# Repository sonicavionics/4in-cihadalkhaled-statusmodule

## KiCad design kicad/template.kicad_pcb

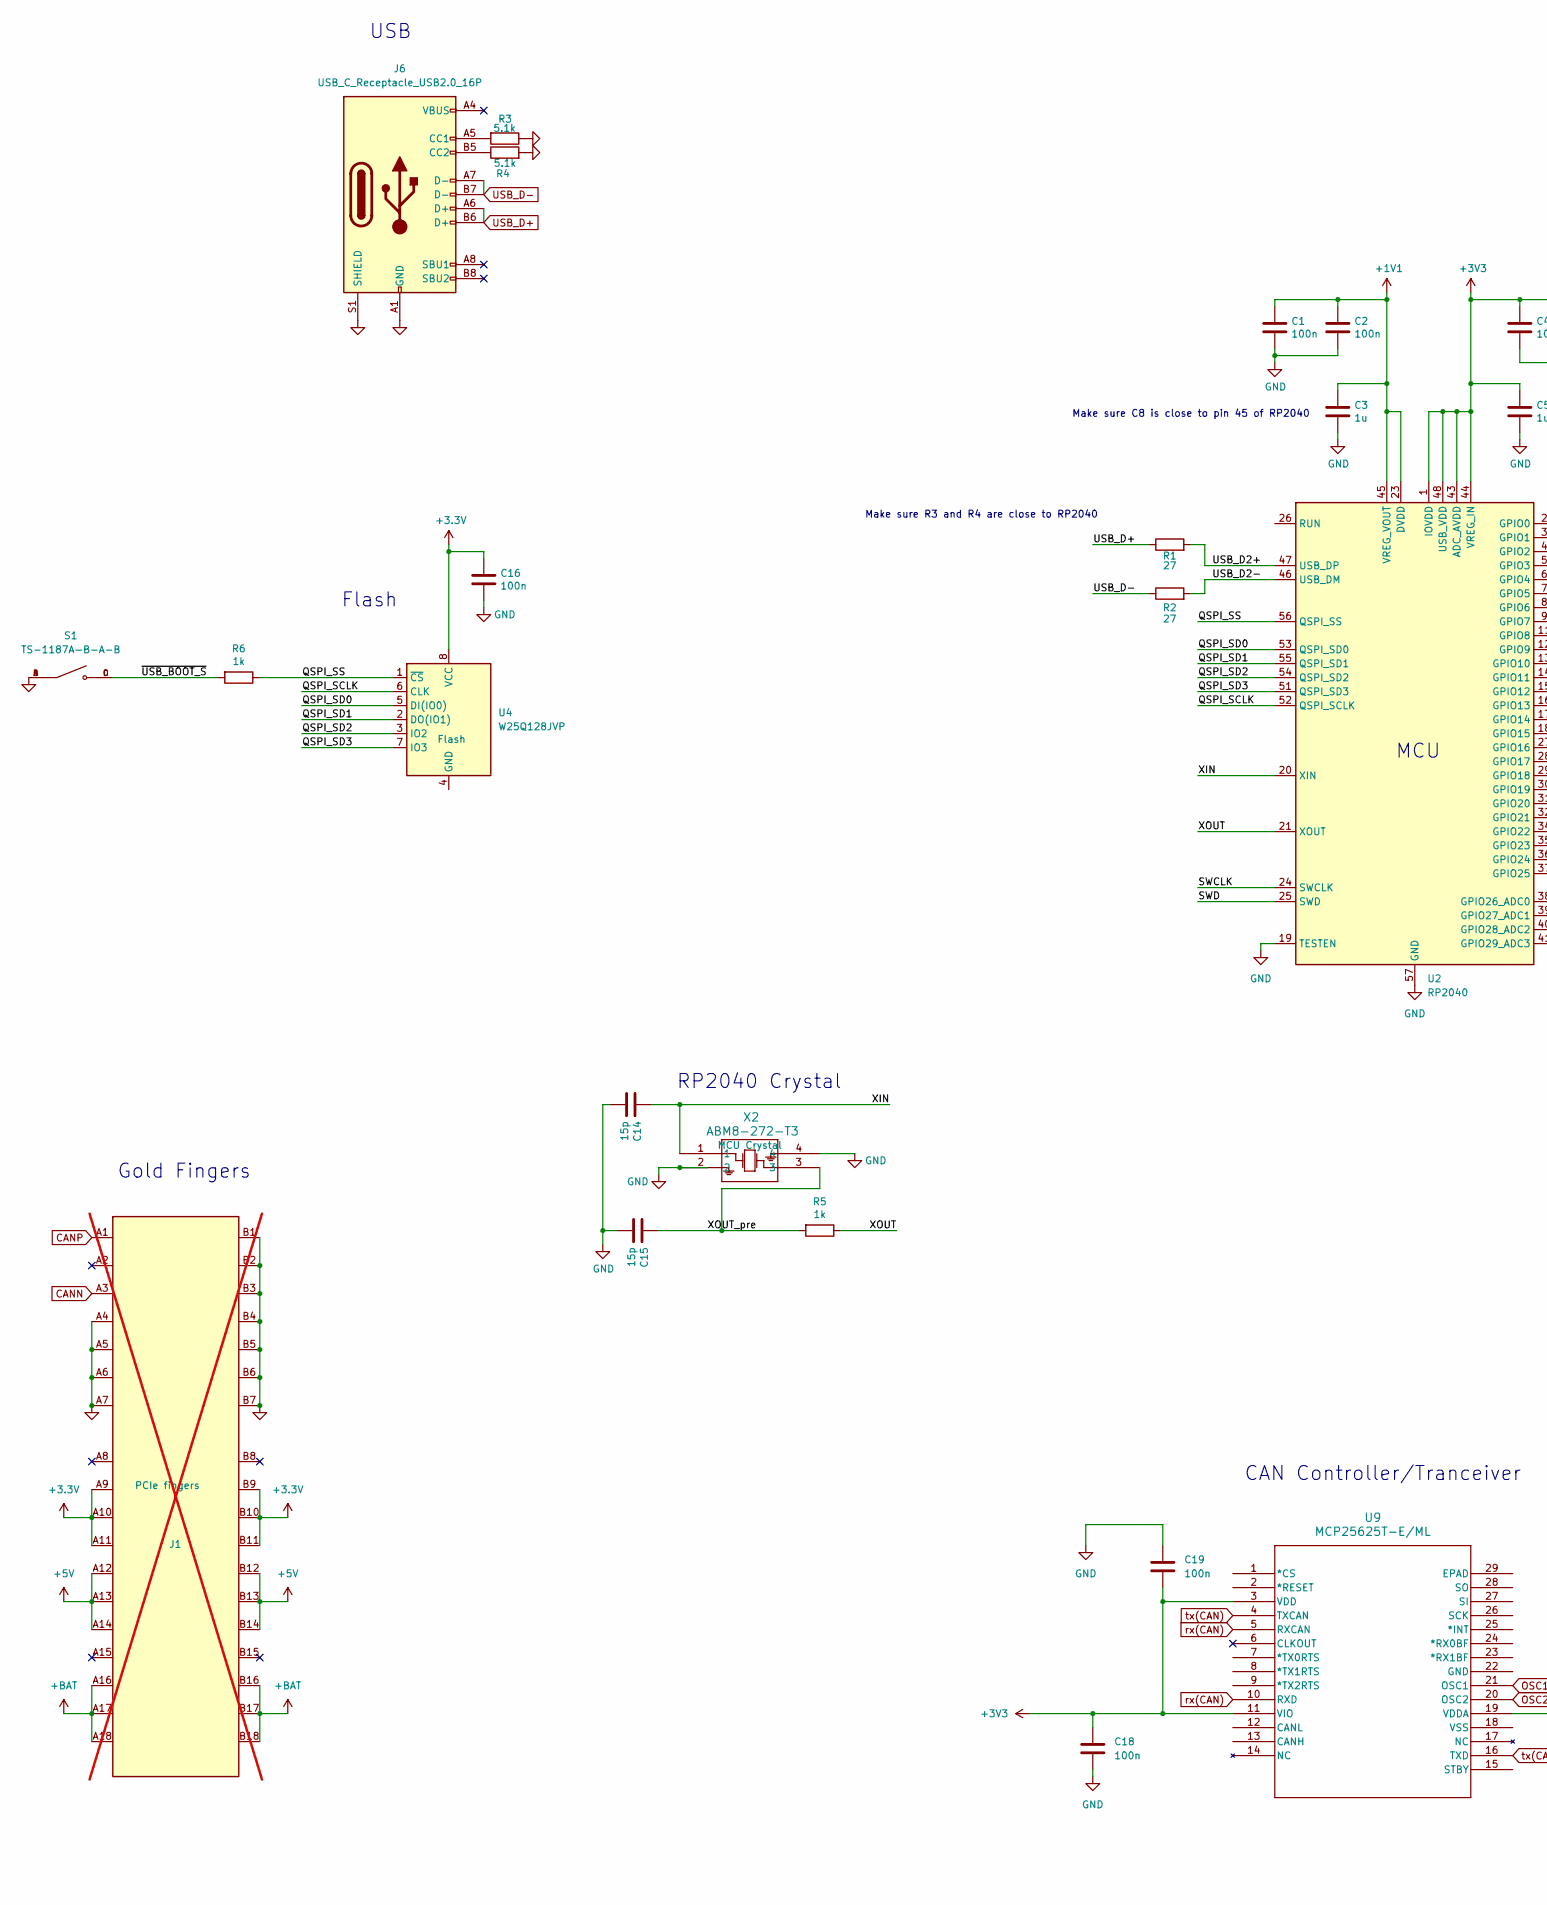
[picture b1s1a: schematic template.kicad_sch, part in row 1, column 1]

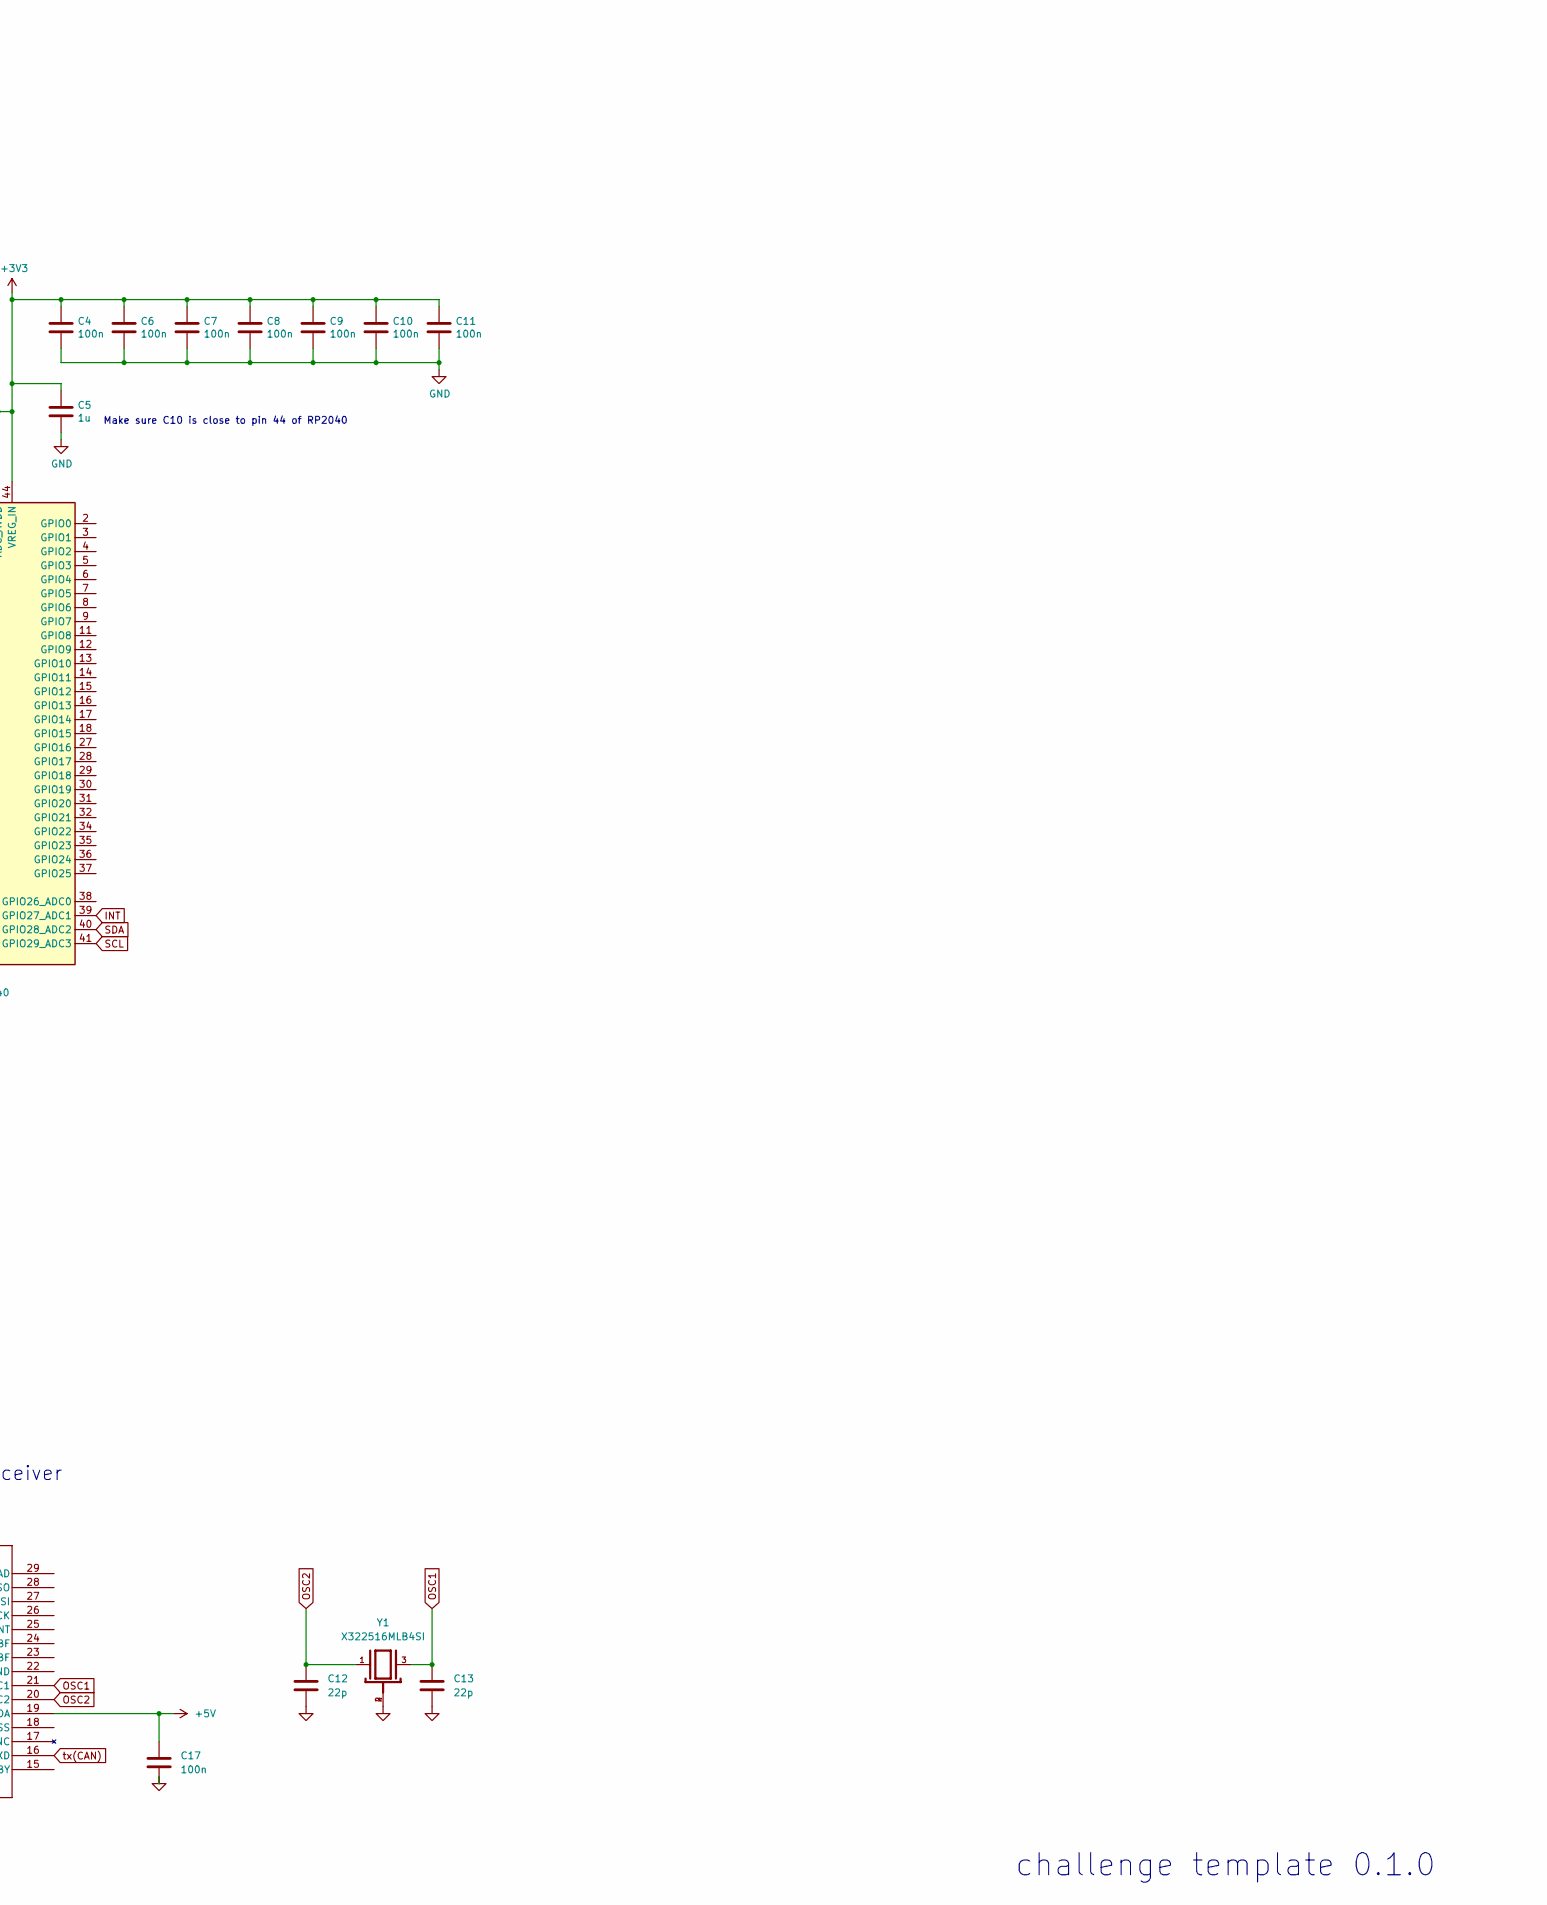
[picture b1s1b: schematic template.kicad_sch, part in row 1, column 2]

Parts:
C1, C2, C4, C6, C7, C8, C9, C10, C11: 100n; C_0402_1005Metric; LCSC C1525
C3, C5: 1u; C_0402_1005Metric; LCSC C52923
C12, C13: 22p; C_0402_1005Metric; LCSC Part # C1555
C14, C15: 15p; C_0402_1005Metric; LCSC Part # C1548
C16, C17, C18, C19: 100n; C_0402_1005Metric; LCSC Part # C307331
J1: Bus_PCI_Express_x1; BUS_PCIexpress_x1; LCSC Part # n/a; not fitted
J6: USB_C_Receptacle_USB2.0_16P; USB_C_Receptacle_Palconn_UTC16-G; LCSC Part # C2765186
R1, R2: 27; R_0402_1005Metric; LCSC Part # C25100
R3, R4: 5.1k; R_0402_1005Metric; LCSC Part # C25905
R5, R6: 1k; R_0402_1005Metric; LCSC Part # C11702
S1: TS-1187A-B-A-B; SW_TS-1187A-B-A-B; PARTREV A0; LCSC Part # C318884
U2: RP2040; QFN-56-1EP_7x7mm_P0.4mm_EP3.2x3.2mm; LCSC C2040
U4: W25Q128JVP; WSON-8-1EP_6x5mm_P1.27mm_EP3.4x4.3mm; LCSC C190862
U9: MCP25625T-E/ML; QFN28_6X6MC_MCH; LCSC Part # C191253
X2: ABM8-272-T3; ABM8-272-T3_ABR; LCSC Part # C20625731
Y1: X322516MLB4SI; OSC_X322516MLB4SI; PARTREV N/A; LCSC Part # C12668

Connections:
+1V1: C1.1, C2.1, C3.1, U2.23 (DVDD), U2.45 (VREG_VOUT), U2.50 (DVDD)
+3.3V: C16.1, J1.A9 (+3.3V), J1.A10 (+3.3V), J1.A11 (~PERST), J1.B9 (JTAG1), J1.B10 (3.3Vaux), J1.B11 (~WAKE), U4.8 (VCC)
+3V3: C4.1, C5.1, C6.1, C7.1, C8.1, C9.1, C10.1, C11.1, C18.1, C19.2, U2.1 (IOVDD), U2.10 (IOVDD), U2.22 (IOVDD), U2.33 (IOVDD), U2.42 (IOVDD), U2.43 (ADC_AVDD), U2.44 (VREG_IN), U2.48 (USB_VDD), U2.49 (IOVDD), U9.3 (VDD), U9.11 (VIO)
+5V: C17.1, J1.A12 (GND), J1.A13 (REFCLK+), J1.A14 (REFCLK-), J1.B12 (RSVD), J1.B13 (GND), J1.B14 (PETp0), U9.19 (VDDA)
+BAT: J1.A16 (PERp0), J1.A17 (PERn0), J1.A18 (GND), J1.B16 (GND), J1.B17 (~PRSNT2), J1.B18 (GND)
/QSPI_SCLK: U2.52 (QSPI_SCLK), U4.6 (CLK)
/QSPI_SD0: U2.53 (QSPI_SD0), U4.5 (DI(IO0))
/QSPI_SD1: U2.55 (QSPI_SD1), U4.2 (DO(IO1))
/QSPI_SD2: U2.54 (QSPI_SD2), U4.3 (IO2)
/QSPI_SD3: U2.51 (QSPI_SD3), U4.7 (IO3)
/QSPI_SS: R6.1, U2.56 (QSPI_SS), U4.1 (~CS)
/SWCLK: U2.24 (SWCLK)
/SWD: U2.25 (SWD)
/USB_D2+: R1.2, U2.47 (USB_DP)
/USB_D2-: R2.2, U2.46 (USB_DM)
/XIN: C14.1, U2.20 (XIN), X2.1
/XOUT: R5.1, U2.21 (XOUT)
/XOUT_pre: C15.1, R5.2, X2.3
/~USB_BOOT_S: R6.2, S1.C, S1.D
CANN: J1.A3 (+12V)
CANP: J1.A1 (~PRSNT1)
GND: C1.2, C2.2, C3.2, C4.2, C5.2, C6.2, C7.2, C8.2, C9.2, C10.2, C11.2, C12.2, C13.2, C14.2, C15.2, C16.2, C17.2, C18.2, C19.1, J1.A4 (GND), J1.A5 (JTAG2), J1.A6 (JTAG3), J1.A7 (JTAG4), J1.B1 (+12V), J1.B2 (+12V), J1.B3 (+12V), J1.B4 (GND), J1.B5 (SMCLK), J1.B6 (SMDAT), J1.B7 (GND), J6.A1 (GND), J6.A12 (GND), J6.B1 (GND), J6.B12 (GND), J6.S1 (SHIELD), R3.1, R4.2, S1.A, S1.B, U2.19 (TESTEN), U2.57 (GND), X2.2, X2.4, Y1.2, Y1.4
INT: U2.39 (GPIO27_ADC1)
unnamed: J6.A5 (CC1), R3.2
unnamed: J6.B5 (CC2), R4.1
OSC1: C13.1, U9.21 (OSC1), Y1.3
OSC2: C12.1, U9.20 (OSC2), Y1.1
SCL: U2.41 (GPIO29_ADC3)
SDA: U2.40 (GPIO28_ADC2)
USB_D+: J6.A6 (D+), J6.B6 (D+), R1.1
USB_D-: J6.A7 (D-), J6.B7 (D-), R2.1
rx(CAN): U9.5 (RXCAN), U9.10 (RXD)
tx(CAN): U9.4 (TXCAN), U9.16 (TXD)

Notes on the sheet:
Make sure C10 is close to pin 44 of RP2040
USB
RP2040 Crystal
MCU
challenge template 0.1.0
Make sure C8 is close to pin 45 of RP2040
Gold Fingers
Make sure R3 and R4 are close to RP2040
CAN Controller/Tranceiver
Flash

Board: 2 copper layers, 31 parts (1 on the bottom side), 25 nets, no tracks yet.

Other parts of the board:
X1: ABM8-272-T3; ABM8-272-T3_ABR

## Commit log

2025-02-28 Update images
2025-03-03 init cihad's status module
